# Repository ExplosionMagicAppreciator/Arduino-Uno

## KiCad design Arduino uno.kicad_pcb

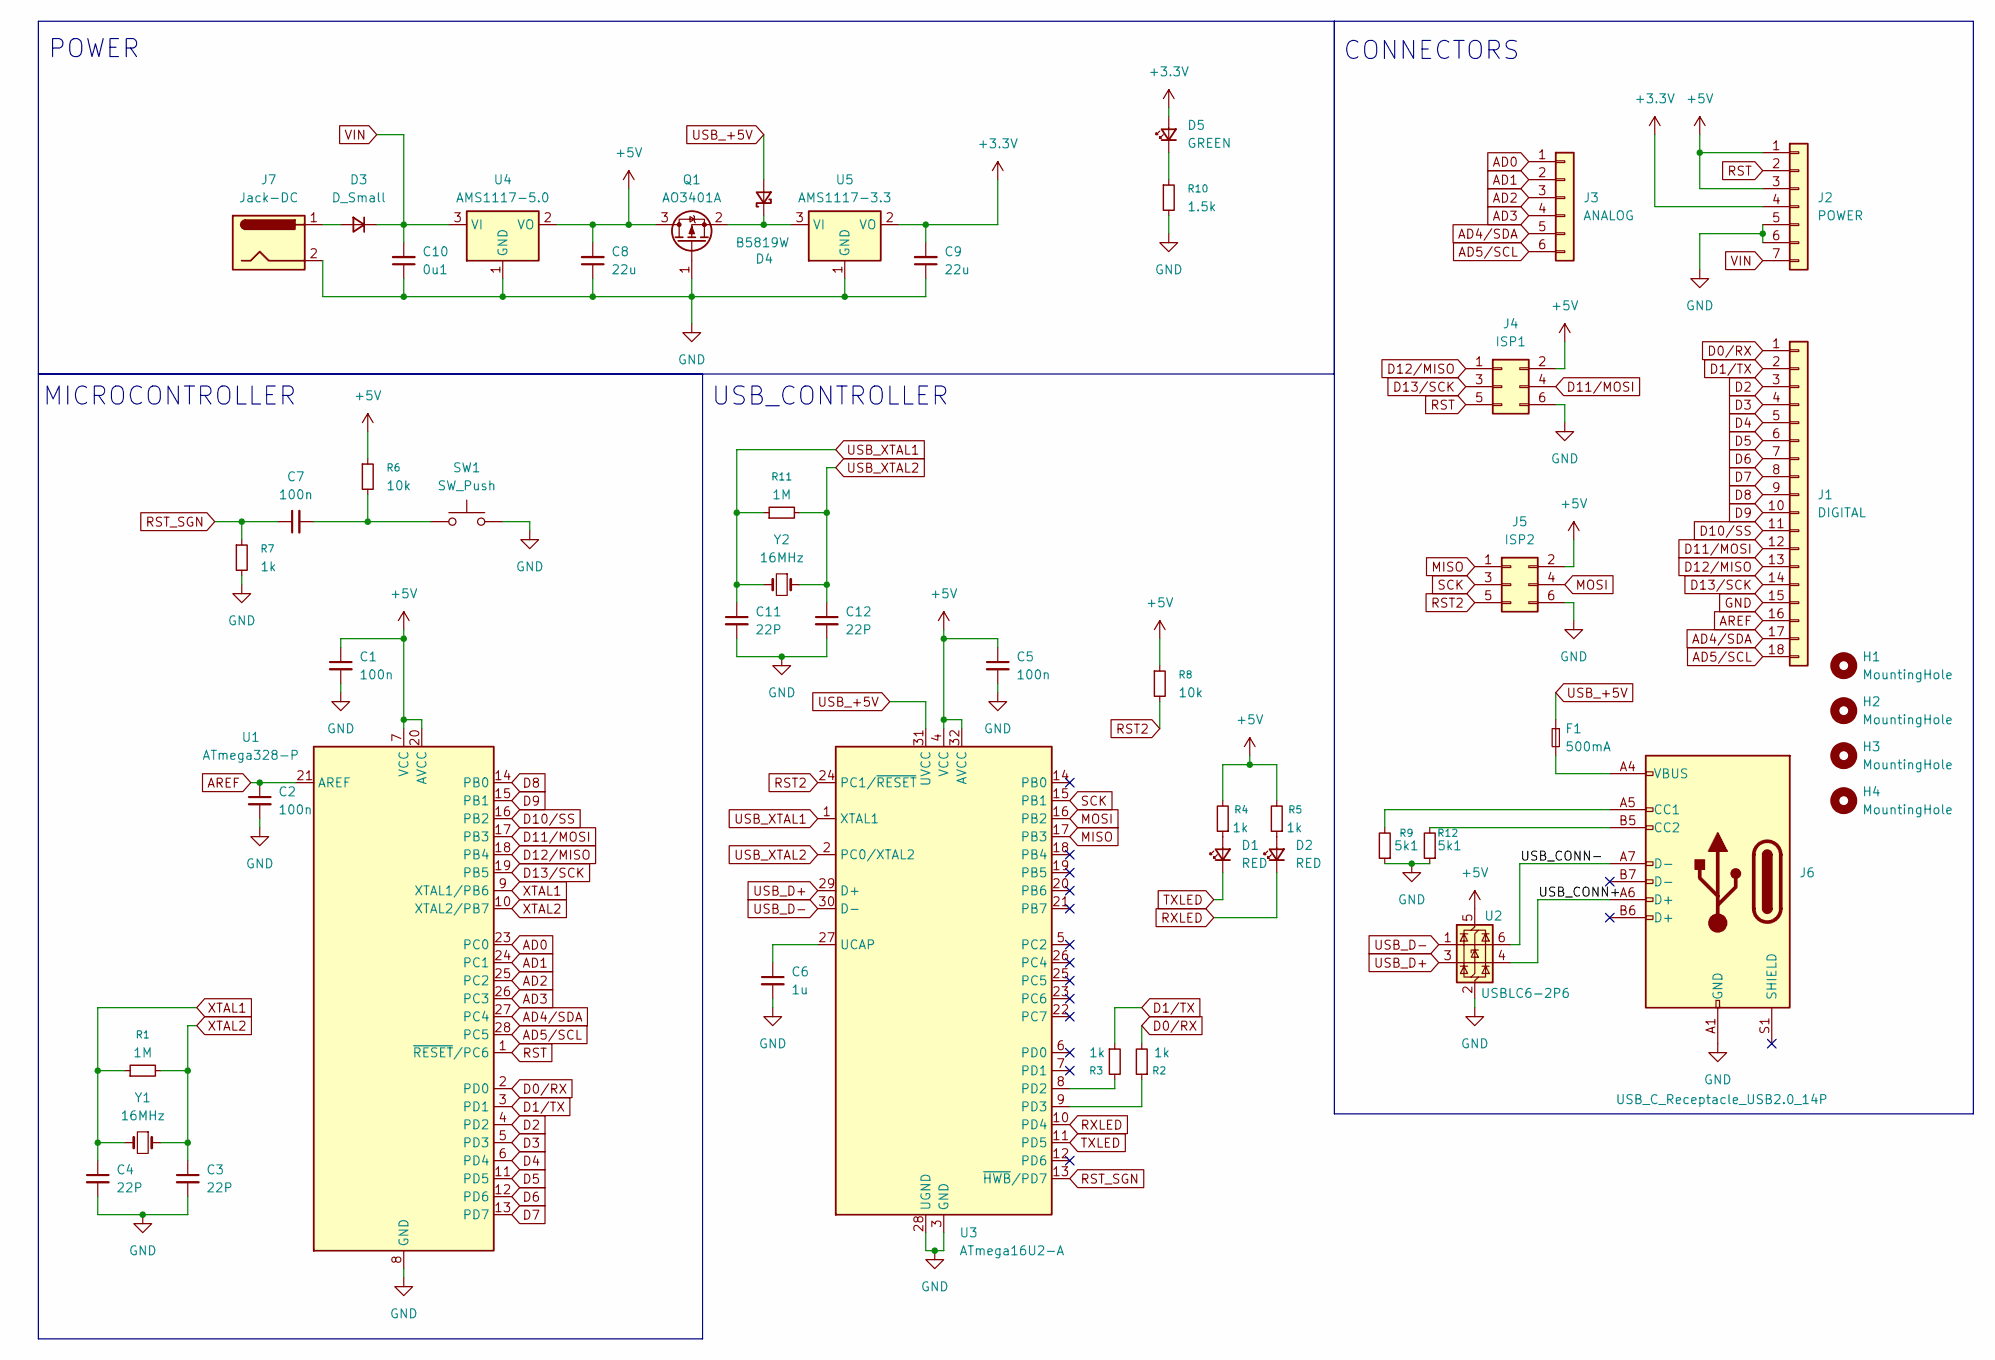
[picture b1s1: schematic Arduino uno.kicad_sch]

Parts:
C1, C2, C5, C7: 100n; C_0402_1005Metric
C3, C4, C11, C12: 22P; C_0402_1005Metric
C6: 1u; C_0201_0603Metric
C8, C9: 22u; C_Elec_4x5.4
C10: 0u1; C_Elec_4x5.4
D1, D2: RED; LED_0603_1608Metric
D3: D_Small; D_PowerDI-123
D4: B5819W; D_SOD-123
D5: GREEN; LED_0603_1608Metric
F1: 500mA; Fuse_1206_3216Metric
H1, H2, H3, H4: MountingHole; MountingHole_3.2mm_M3
J1: DIGITAL; PinSocket_1x18_P2.54mm_Vertical
J2: POWER; PinSocket_1x07_P2.54mm_Vertical
J3: ANALOG; PinSocket_1x06_P2.54mm_Vertical
J4: ISP1; PinHeader_2x03_P2.54mm_Vertical
J5: ISP2; PinHeader_2x03_P2.54mm_Vertical
J6: USB_C_Receptacle_USB2.0_14P; USB_C_Receptacle_GCT_USB4105-xx-A_16P_TopMnt_Horizontal
J7: Jack-DC; BarrelJack_GCT_DCJ200-10-A_Horizontal
Q1: AO3401A; SOT-23
R1, R11: 1M; R_0402_1005Metric
R2, R3, R7: 1k; R_0402_1005Metric
R4, R5: 1k; R_0603_1608Metric
R6, R8: 10k; R_0402_1005Metric
R9, R12: 5k1; R_0603_1608Metric_Pad0.98x0.95mm_HandSolder
R10: 1.5k; R_0603_1608Metric
SW1: SW_Push; SW_Push_1TS009xxxx-xxxx-xxxx_6x6x5mm
U1: ATmega328-P; DIP-28_W7.62mm_Socket
U2: USBLC6-2P6; SOT-666
U3: ATmega16U2-A; TQFP-32_7x7mm_P0.8mm
U4: AMS1117-5.0; SOT-223-3_TabPin2
U5: AMS1117-3.3; SOT-223-3_TabPin2
Y1, Y2: 16MHz; Crystal_SMD_TXC_7M-4Pin_3.2x2.5mm

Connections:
+3.3V: C9.2, D5.2 (A), J2.4, U5.2 (VO)
+5V: C1.1, C5.1, C8.2, J2.1, J2.3, J4.2, J5.2, Q1.3 (D), R4.2, R5.2, R6.1, R8.1, U1.7 (VCC), U1.20 (AVCC), U2.5 (VBUS), U3.4 (VCC), U3.32 (AVCC), U4.2 (VO)
/USB_CONN+: J6.A6 (D+), U2.4 (I/O2)
/USB_CONN-: J6.A7 (D-), U2.6 (I/O1)
AD0: J3.1, U1.23 (PC0)
AD1: J3.2, U1.24 (PC1)
AD2: J3.3, U1.25 (PC2)
AD3: J3.4, U1.26 (PC3)
AD4/SDA: J1.17, J3.5, U1.27 (PC4)
AD5/SCL: J1.18, J3.6, U1.28 (PC5)
AREF: C2.1, J1.16, U1.21 (AREF)
D0/RX: J1.1, R2.2, U1.2 (PD0)
D1/TX: J1.2, R3.1, U1.3 (PD1)
D2: J1.3, U1.4 (PD2)
D3: J1.4, U1.5 (PD3)
D4: J1.5, U1.6 (PD4)
D5: J1.6, U1.11 (PD5)
D6: J1.7, U1.12 (PD6)
D7: J1.8, U1.13 (PD7)
D8: J1.9, U1.14 (PB0)
D9: J1.10, U1.15 (PB1)
D10/SS: J1.11, U1.16 (PB2)
D11/MOSI: J1.12, J4.4, U1.17 (PB3)
D12/MISO: J1.13, J4.1, U1.18 (PB4)
D13/SCK: J1.14, J4.3, U1.19 (PB5)
GND: C1.2, C2.2, C3.2, C4.2, C5.2, C6.2, C8.1, C9.1, C10.1, C11.2, C12.2, J1.15, J2.5, J2.6, J4.6, J5.6, J6.A1 (GND), J6.A12 (GND), J6.B1 (GND), J6.B12 (GND), J7.2, Q1.1 (G), R7.2, R9.1, R10.2, R12.1, SW1.2, U1.8 (GND), U1.22 (GND), U2.2 (GND), U3.3 (GND), U3.28 (UGND), U4.1 (GND), U5.1 (GND)
MISO: J5.1, U3.17 (PB3)
MOSI: J5.4, U3.16 (PB2)
unnamed: C7.2, R6.2, SW1.1
unnamed: D1.2 (A), R4.1
unnamed: D2.2 (A), R5.1
unnamed: D3.2 (A), J7.1
unnamed: D4.1 (K), Q1.2 (S), U5.3 (VI)
unnamed: D5.1 (K), R10.1
unnamed: F1.2, J6.A4 (VBUS), J6.A9 (VBUS), J6.B4 (VBUS), J6.B9 (VBUS)
unnamed: J6.A5 (CC1), R9.2
unnamed: J6.B5 (CC2), R12.2
unnamed: R3.2, U3.8 (PD2)
unnamed: R2.1, U3.9 (PD3)
unnamed: C6.1, U3.27 (UCAP)
RST: J2.2, J4.5, U1.1 (~RESET/PC6)
RST2: J5.5, R8.2, U3.24 (PC1/~RESET)
RST_SGN: C7.1, R7.1, U3.13 (~HWB/PD7)
RXLED: D2.1 (K), U3.10 (PD4)
SCK: J5.3, U3.15 (PB1)
TXLED: D1.1 (K), U3.11 (PD5)
USB_+5V: D4.2 (A), F1.1, U3.31 (UVCC)
USB_D+: U2.3 (I/O2), U3.29 (D+)
USB_D-: U2.1 (I/O1), U3.30 (D-)
USB_XTAL1: C11.1, R11.1, U3.1 (XTAL1), Y2.2
USB_XTAL2: C12.1, R11.2, U3.2 (PC0/XTAL2), Y2.1
VIN: C10.2, D3.1 (K), J2.7, U4.3 (VI)
XTAL1: C4.1, R1.1, U1.9 (XTAL1/PB6), Y1.2
XTAL2: C3.1, R1.2, U1.10 (XTAL2/PB7), Y1.1

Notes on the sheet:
CONNECTORS
MICROCONTROLLER
USB_CONTROLLER
POWER

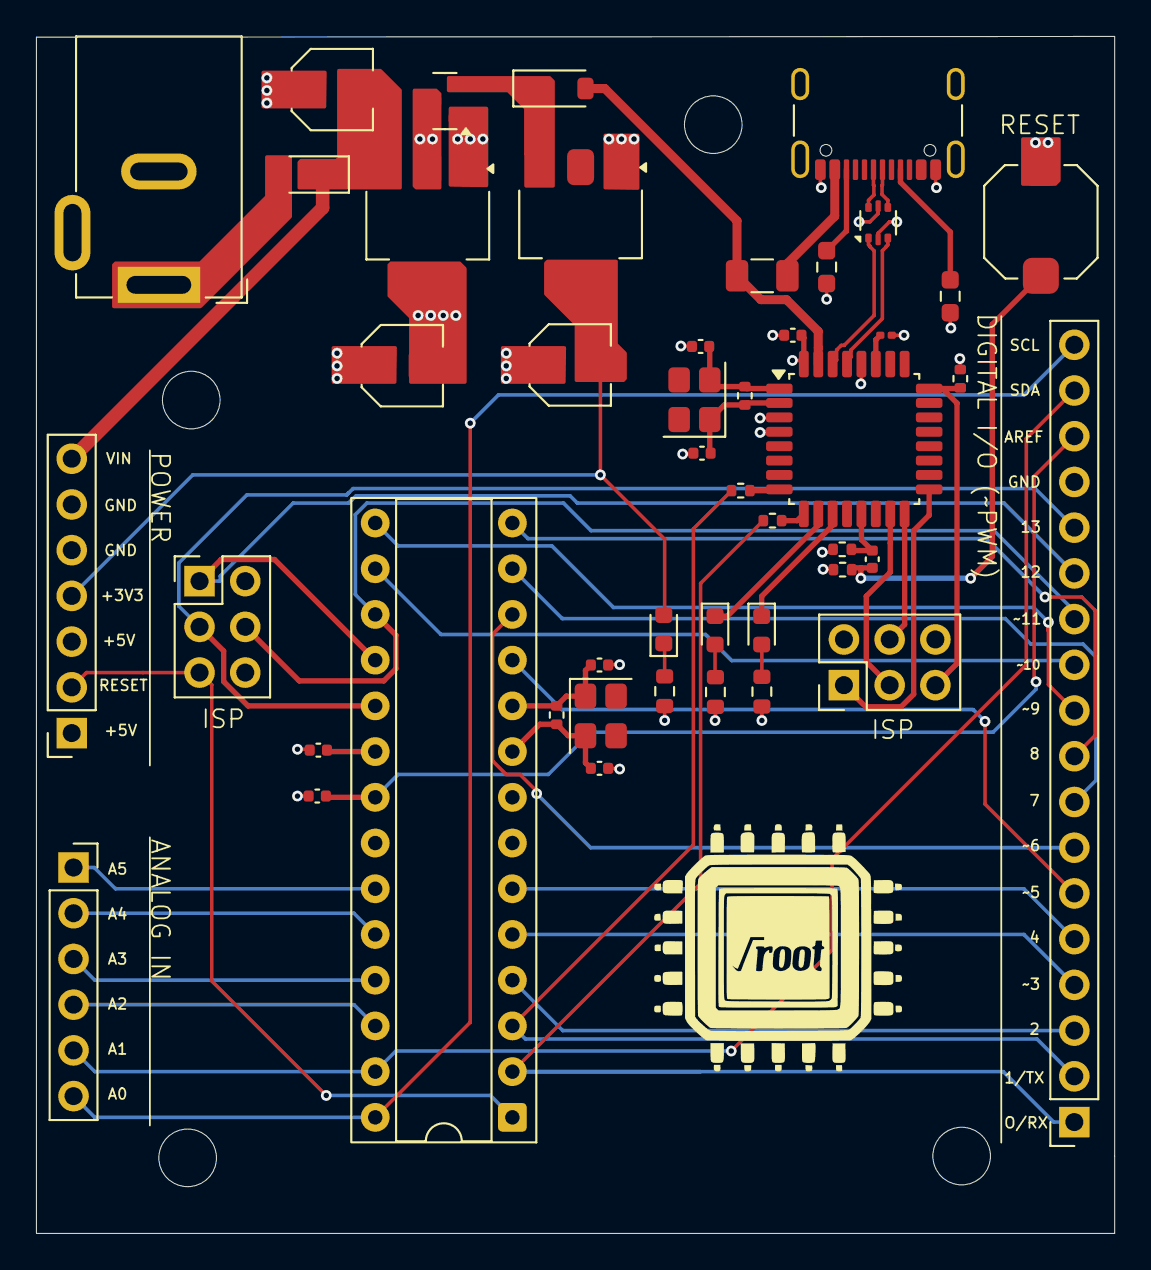
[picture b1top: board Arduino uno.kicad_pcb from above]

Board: 4 copper layers, 59.9 x 66.5 mm, 50 parts (0 on the bottom side), 54 nets.

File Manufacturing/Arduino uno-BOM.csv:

"Reference","Qty","Value","DNP","Exclude from BOM","Exclude from Board","Footprint","Datasheet"
"C1,C2,C5,C7","4","100n","","","","Capacitor_SMD:C_0402_1005Metric","~"
"C3,C4,C11,C12","4","22P","","","","Capacitor_SMD:C_0402_1005Metric","~"
"C6","1","1u","","","","Capacitor_SMD:C_0201_0603Metric","~"
"C8,C9","2","22u","","","","Capacitor_SMD:C_Elec_4x5.4","~"
"C10","1","0u1","","","","Capacitor_SMD:C_Elec_4x5.4","~"
"D1,D2","2","RED","","","","LED_SMD:LED_0603_1608Metric","~"
"D3","1","D_Small","","","","Diode_SMD:D_PowerDI-123","~"
"D4","1","B5819W","","","","Diode_SMD:D_SOD-123","~"
"D5","1","GREEN","","","","LED_SMD:LED_0603_1608Metric","~"
"F1","1","500mA","","","","Fuse:Fuse_1206_3216Metric","~"
"J1","1","DIGITAL","","","","Connector_PinSocket_2.54mm:PinSocket_1x18_P2.54mm_Vertical","~"
"J2","1","POWER","","","","Connector_PinSocket_2.54mm:PinSocket_1x07_P2.54mm_Vertical","~"
"J3","1","ANALOG","","","","Connector_PinSocket_2.54mm:PinSocket_1x06_P2.54mm_Vertical","~"
"J4","1","ISP1","","","","Connector_PinHeader_2.54mm:PinHeader_2x03_P2.54mm_Vertical","~"
"J5","1","ISP2","","","","Connector_PinHeader_2.54mm:PinHeader_2x03_P2.54mm_Vertical","~"
"J6","1","USB_C_Receptacle_USB2.0_14P","","","","Connector_USB:USB_C_Receptacle_GCT_USB4105-xx-A_16P_TopMnt_Horizontal","https://www.usb.org/sites/default/files/documents/usb_type-c.zip"
"J7","1","Jack-DC","","","","Connector_BarrelJack:BarrelJack_GCT_DCJ200-10-A_Horizontal","~"
"Q1","1","AO3401A","","","","Package_TO_SOT_SMD:SOT-23","http://www.aosmd.com/pdfs/datasheet/AO3401A.pdf"
"R1,R11","2","1M","","","","Resistor_SMD:R_0402_1005Metric","~"
"R2,R3,R7","3","1k","","","","Resistor_SMD:R_0402_1005Metric","~"
"R4,R5","2","1k","","","","Resistor_SMD:R_0603_1608Metric","~"
"R6,R8","2","10k","","","","Resistor_SMD:R_0402_1005Metric","~"
"R9,R12","2","5k1","","","","Resistor_SMD:R_0603_1608Metric_Pad0.98x0.95mm_HandSolder","~"
"R10","1","1.5k","","","","Resistor_SMD:R_0603_1608Metric","~"
"SW1","1","SW_Push","","","","Button_Switch_SMD:SW_Push_1TS009xxxx-xxxx-xxxx_6x6x5mm","~"
"U1","1","ATmega328-P","","","","Package_DIP:DIP-28_W7.62mm_Socket","http://ww1.microchip.com/downloads/en/DeviceDoc/ATmega328_P%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"
"U2","1","USBLC6-2P6","","","","Package_TO_SOT_SMD:SOT-666","https://www.st.com/resource/en/datasheet/usblc6-2.pdf"
"U3","1","ATmega16U2-A","","","","Package_QFP:TQFP-32_7x7mm_P0.8mm","http://ww1.microchip.com/downloads/en/DeviceDoc/doc7799.pdf"
"U4","1","AMS1117-5.0","","","","Package_TO_SOT_SMD:SOT-223-3_TabPin2","http://www.advanced-monolithic.com/pdf/ds1117.pdf"
"U5","1","AMS1117-3.3","","","","Package_TO_SOT_SMD:SOT-223-3_TabPin2","http://www.advanced-monolithic.com/pdf/ds1117.pdf"
"Y1,Y2","2","16MHz","","","","Crystal:Crystal_SMD_TXC_7M-4Pin_3.2x2.5mm","~"
